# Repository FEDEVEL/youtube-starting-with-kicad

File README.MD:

### Description
This project is used in the following video:
* What is KiCad about? Starting with KiCad ... https://youtu.be/maaBkw7IRUc

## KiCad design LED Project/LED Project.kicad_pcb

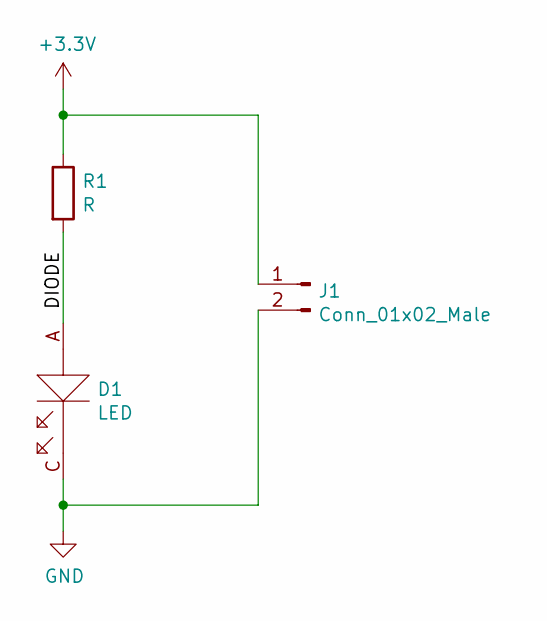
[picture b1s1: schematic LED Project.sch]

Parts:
D1: LED; LED0603
J1: Conn_01x02_Male; Molex_KK-254_AE-6410-02A_1x02_P2.54mm_Vertical
R1: R; R_0805_2012Metric

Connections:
+3V3: J1.1, R1.1
/DIODE: D1.A (Anode), R1.2
GND: D1.C (Cathode), J1.2

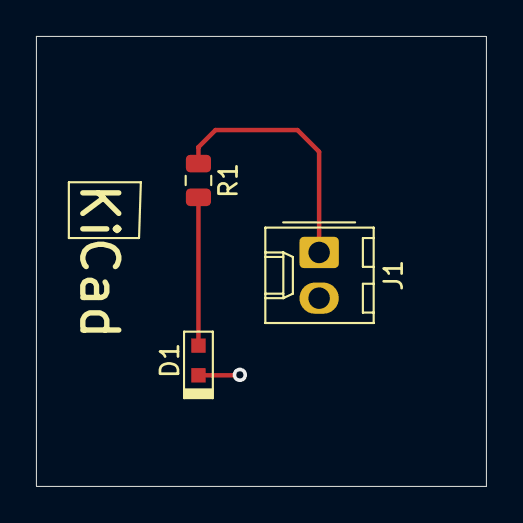
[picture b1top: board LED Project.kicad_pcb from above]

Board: 2 copper layers, 25.0 x 25.0 mm, 3 parts (0 on the bottom side), 3 nets.

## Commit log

2020-07-27 Readme added
